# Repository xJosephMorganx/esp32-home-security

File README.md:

# ESP32 Home Security

**Four custom-built modules. One touchscreen hub. Local control over ESP-NOW.**

A modular residential monitoring project combining embedded software, custom KiCad PCBs, enclosure design, and local manufacturing. Four independent ESP32 firmwares connect a touchscreen hub, magnetic door sensor, PIR motion sensor, and RFID reader.

The hub owns the system state and card authorization. Sensor nodes report observations; the RFID reader requests actions. Internet services add WhatsApp, Messenger, and email notifications without being required for local supervision.

**Project status:** the latest project report documents completed hardware and successful functional integration of the four modules. It reports touch/RFID arming, card management, and notification delivery. These are project-reported hardware results, not automated test results or quantified reliability measurements.

## Highlights

- **Touchscreen control:** English UI on a 3.2-inch ILI9341 display with FT6336 capacitive touch, presented in 320 × 240 landscape.
- **Distributed sensing:** MC-38 door contact and PIR motion detection with filtering and explicit unknown/offline states.
- **RFID management:** hub-side authorization, enrollment, removal, and persistent storage for up to 32 card UIDs.
- **Encrypted local links:** provisioned ESP-NOW unicast peers, per-pair LMKs, application acknowledgements, deduplication, and automatic channel recovery.
- **Remote notifications:** WhatsApp and Messenger through CallMeBot; email through a Google Apps Script web app.
- **Local feedback:** confirmed-state LEDs, recent event history, and a red full-screen event alert with touch dismissal.
- **Clock and weather:** NTP time and Open-Meteo weather, with unavailable and stale-data indicators.

## Architecture

```mermaid
flowchart LR
    Door[Door sensor · MC-38] <-->|Encrypted ESP-NOW| Hub[ESP32 touchscreen hub]
    PIR[PIR motion sensor] <-->|Encrypted ESP-NOW| Hub
    RFID[RFID reader · RC522] <-->|Encrypted ESP-NOW| Hub
    Hub -->|Wi-Fi / HTTPS| Messages[CallMeBot · WhatsApp / Messenger]
    Hub -->|Wi-Fi / HTTPS| Email[Google Apps Script · Email]
    Hub -->|Wi-Fi| Services[NTP clock / Open-Meteo weather]
```

| Module | Responsibility | User feedback |
| --- | --- | --- |
| [Hub](firmware/hub/) | Global state, sensor supervision, card authorization, UI, and network services | Touchscreen and remote notifications |
| [Door](firmware/door/) | Debounce and report the magnetic contact | LED on only when armed and connected |
| [PIR](firmware/pir/) | Sensor warm-up, filtering, and motion reports | LED on only when armed and connected |
| [RFID](firmware/rfid/) | Read card presence and request actions from the hub | Green: disarmed; red: armed; both off without confirmed state |

Nodes do not need to join the router. When the hub is associated with Wi-Fi, ESP-NOW shares its channel. Nodes recover the channel through scanning and validated synchronization. Loss of internet does not itself disable local operation, although Wi-Fi association and channel changes can temporarily interrupt radio traffic.

The shared [application protocol](firmware/common/PROTOCOL.md) defines explicit binary serialization, session/sequence handling, retries, and `STATE_SYNC` acknowledgements. The [RFID contract](firmware/common/RFID_CONTRACT.md) adds short-lived operation contexts and correlated results. An ESP-NOW send callback alone is not proof that the hub processed an action.

## How it behaves

The hub starts **disarmed** after every reboot. Arming requires at least one connected sensor: door or PIR. RFID connectivity does not satisfy that requirement. Disarming does not require an online sensor.

An open door, active motion, or PIR warm-up does not independently block arming. While armed, admitted events can produce notifications and a red visual alert. The controller stays armed: although the protocol defines `ALARM` and `EXIT_DELAY`, the current controller does not transition into those states.

The UI provides **Home**, **Events**, **Nodes**, and **Setup**. Settings include diagnostics, touch testing, access cards, and notification tests. Card enrollment follows **Setup → Access cards → Add card → Scan card** and opens a 30-second enrollment window. Enrollment does not arm the system.

| Parameter | Current configuration / behavior |
| --- | --- |
| Link heartbeat / timeout | 5 seconds / 15 seconds |
| Report retries | Up to 3 transmissions, 250 ms apart |
| Channel search | 1 second per channel; not a total recovery-time guarantee |
| Door debounce | 40 ms |
| PIR setup in the reported build | 30-second warm-up, 10 ms sampling, 50 ms stability filter |
| RFID operation context / card removal | 5-second validity / 500 ms confirmed absence |
| Card storage | Up to 32 UIDs in a versioned, CRC-checked NVS blob |
| Event history | 16 entries in RAM |
| Notification queues | 16 entries per channel, expiring after 10 minutes |
| Visual alert | 10 seconds after drawing completes, or tap to close |

PIR electrical behavior and timing must be configured locally; the public template deliberately leaves unconfirmed settings unset. Queue contents and event history do not survive a reboot. Provider acceptance does not prove message receipt or reading.

## Repository layout

```text
firmware/
├── common/     Shared protocol library, contracts, and tests
├── hub/        Display, touch, state controller, radio, RFID authority, networking
├── door/       Door contact firmware and logic tests
├── pir/        PIR firmware, diagnostics, and tests
└── rfid/       RC522 firmware, diagnostics, and tests
hardware/
├── kicad/      Schematics, PCB layouts, and associated exports
├── hub/        Module manufacturing files
├── door/       Module manufacturing files
├── pir/        Module manufacturing files
└── rfid/       Module manufacturing files
```

Manufacturing assets include LightBurn laser projects and DXF files for CNC preparation. The STEP file alongside the door KiCad project is a **PCB 3D export**, not an enclosure model. The report describes enclosure design and completed assemblies; only files actually present in this repository are distributed here.

## Development environment

The report and inspected local environment identify the following baseline:

| Component | Version / source |
| --- | --- |
| Target | Classic ESP32, Arduino C++ |
| Arduino-ESP32 | 3.3.10 |
| Arduino CLI | 1.5.0 in the inspected environment |
| DomoticaProtocol | 1.2.0, included in `firmware/common` |
| MFRC522 | 1.4.12 |
| Adafruit GFX | 1.12.6 in the inspected environment |
| Adafruit BusIO | 1.17.4 in the inspected environment |
| Hub firmware identifier | `hub-wa-0.6.0` |
| Display / touch | Local SPI display driver and bundled FT6336 driver |

Wi-Fi, ESP-NOW, FreeRTOS, NVS, HTTPS, certificate-bundle support, and cJSON come from the ESP32 environment. The hub uses Adafruit GFX for drawing primitives; it does not use the manufacturer's TFT_eSPI or LVGL demo as its display initialization.

### Configure your own devices

Clone the repository, install the ESP32 board support and listed Arduino libraries, then create local configuration files from the templates:

| Module | Copy this template | To this ignored local file |
| --- | --- | --- |
| Hub Wi-Fi | `firmware/hub/secrets.example.h` | `firmware/hub/secrets.h` |
| Hub radio | `firmware/hub/radio_secrets.example.h` | `firmware/hub/radio_secrets.h` |
| WhatsApp | `firmware/hub/whatsapp_secrets.example.h` | `firmware/hub/whatsapp_secrets.h` |
| Messenger | `firmware/hub/messenger_secrets.example.h` | `firmware/hub/messenger_secrets.h` |
| Email | `firmware/hub/email_secrets.example.h` | `firmware/hub/email_secrets.h` |
| Door | `firmware/door/config.example.h` | `firmware/door/config.local.h` |
| PIR | `firmware/pir/config.example.h` | `firmware/pir/config.local.h` |
| RFID | `firmware/rfid/config.example.h` | `firmware/rfid/config.local.h` |

Provision your own STA MAC addresses, explicit PMK, and unique LMK for each hub/node pair. Matching peers must use compatible keys. Some public node examples retain a project-specific hub MAC: replace it with your own; it is not a discovery default. Verify input polarity, LED polarity, sensor readiness settings, and permitted channels before enabling provisioned operation. Empty or invalid credentials do not enable an unencrypted fallback.

Configure only the notification channels you intend to use. Email requires a separately deployed Google Apps Script endpoint with `HUB_SECRET` and `EMAIL_TO` properties; that deployment is not included in this repository. Keep the matching shared secret in the ignored hub configuration. Never put real Wi-Fi credentials, notification API keys, phone numbers, or radio keys in example files.

### Build and upload

Each module is a separate sketch. From the repository root, supply the shared library explicitly, for example:

```sh
arduino-cli compile --fqbn esp32:esp32:esp32 --library ./firmware/common ./firmware/hub
arduino-cli compile --fqbn esp32:esp32:esp32 --library ./firmware/common ./firmware/door
arduino-cli compile --fqbn esp32:esp32:esp32 --library ./firmware/common ./firmware/pir
arduino-cli compile --fqbn esp32:esp32:esp32 --library ./firmware/common ./firmware/rfid
```

Use the board definition and flash settings appropriate to your ESP32 board. Upload each sketch to its corresponding module using Arduino IDE or Arduino CLI and the actual serial port. The external enclosure USB-C connector supplies power only; the report describes opening the enclosure to reach the ESP32 programming port.

These commands are build instructions, not a claim that a fresh build or hardware test was run for this README. Source-level tests are included under each module's `tests/` directory and under `firmware/common/tests/`.

## Hardware and fabrication

The reported assemblies use four custom single-sided PCBs, separate enclosures, and individual 5 V supplies through two-wire USB-C power connectors. The RC522 operates from 3.3 V. PCB preparation combines KiCad design, laser removal of a paint mask, chemical etching, UV solder mask, and CNC drilling/outline cutting.

The hub's fixed PCB wiring is:

| Interface | GPIO assignments |
| --- | --- |
| LCD | CS 18, RST 19, DC 21, MOSI 22, SCK 23, MISO 33, backlight 32 |
| Touch | SCL 25, RST 26, SDA 27, INT 14 |
| Unused SD select | CS 13, held high |

The LCD runs at 1 MHz SPI; touch uses 100 kHz I2C. Do not replace these assignments with manufacturer demo wiring.

For RFID, the latest report and [current board definitions](firmware/rfid/board_pins.h) agree on SS 17, RST 23, SCK 18, MISO 21, MOSI 19, and IRQ 22, with green/red LEDs on 25/26. These differ from an older project context table (SS 21, RST 22, MISO 19, MOSI 23); the source records an explicit user correction. Confirm the actual board wiring before reproducing the assembly.

## Validation and limitations

The latest project report, *Sistema modular de domótica y seguridad residencial con ESP32*, documents completed assemblies and functional checks of inter-module communication, touch/RFID arming and disarming, card management, WhatsApp/Messenger/email notifications, and visual-alert dismissal. The report is maintained outside the public repository.

The project is an academic monitoring prototype, with these documented limits:

- Touch controls and card administration have no PIN or administrator authentication.
- RFID authorization uses a card UID, which can be copied; it is not cryptographic card authentication.
- The system starts disarmed after reboot and has no battery backup, siren, or physical lock actuator.
- Event history and notification queues are bounded and volatile; remote delivery depends on external services.
- Radio recovery can involve interruptions. No measured range, latency, packet-loss, or power-consumption figures are claimed.
- Touch-panel electrical levels have not been fully characterized across operating conditions.
- No residential alarm, electrical, or environmental certification is claimed.

## What is kept local

The public repository includes firmware, configuration examples, protocol documentation, tests, and hardware/manufacturing sources. `.gitignore` excludes real secrets, local node configuration, build outputs, caches, KiCad internal histories/preferences, `AGENTS.md`, and the root `docs/`, `escuela/`, and `references/` folders.

The original manufacturer package and academic report are not bundled. Removing a file from tracking does not remove it from earlier commits; older context and reference files remain in repository history.

## Third-party notices

Preserve notices in bundled source files and the [font license](firmware/hub/FONT_LICENSE.txt). External dependencies retain their own licenses. No repository-wide license has been declared.

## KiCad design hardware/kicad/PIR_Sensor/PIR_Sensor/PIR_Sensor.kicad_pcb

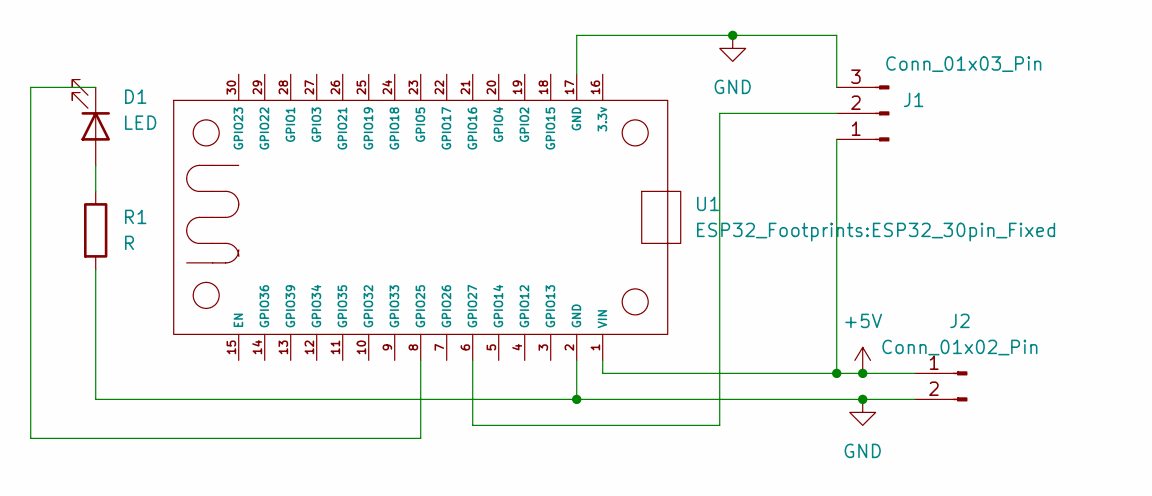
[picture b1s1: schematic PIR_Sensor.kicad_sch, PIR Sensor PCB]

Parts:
D1: LED; LED_D5.0mm
J1: Conn_01x03_Pin; PinHeader_1x03_P2.54mm_Vertical
J2: Conn_01x02_Pin; PinHeader_1x02_P2.54mm_Vertical
R1: R; R_Axial_DIN0207_L6.3mm_D2.5mm_P7.62mm_Horizontal
U1: ESP32_30pin_Fixed

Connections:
+5V: J1.1, J2.1, U1.1 (VIN)
GND: J1.3, J2.2, R1.2, U1.2 (GND), U1.17 (GND)
unnamed: D1.2 (A), R1.1
unnamed: D1.1 (K), U1.8 (GPIO25)
unnamed: J1.2, U1.6 (GPIO27)

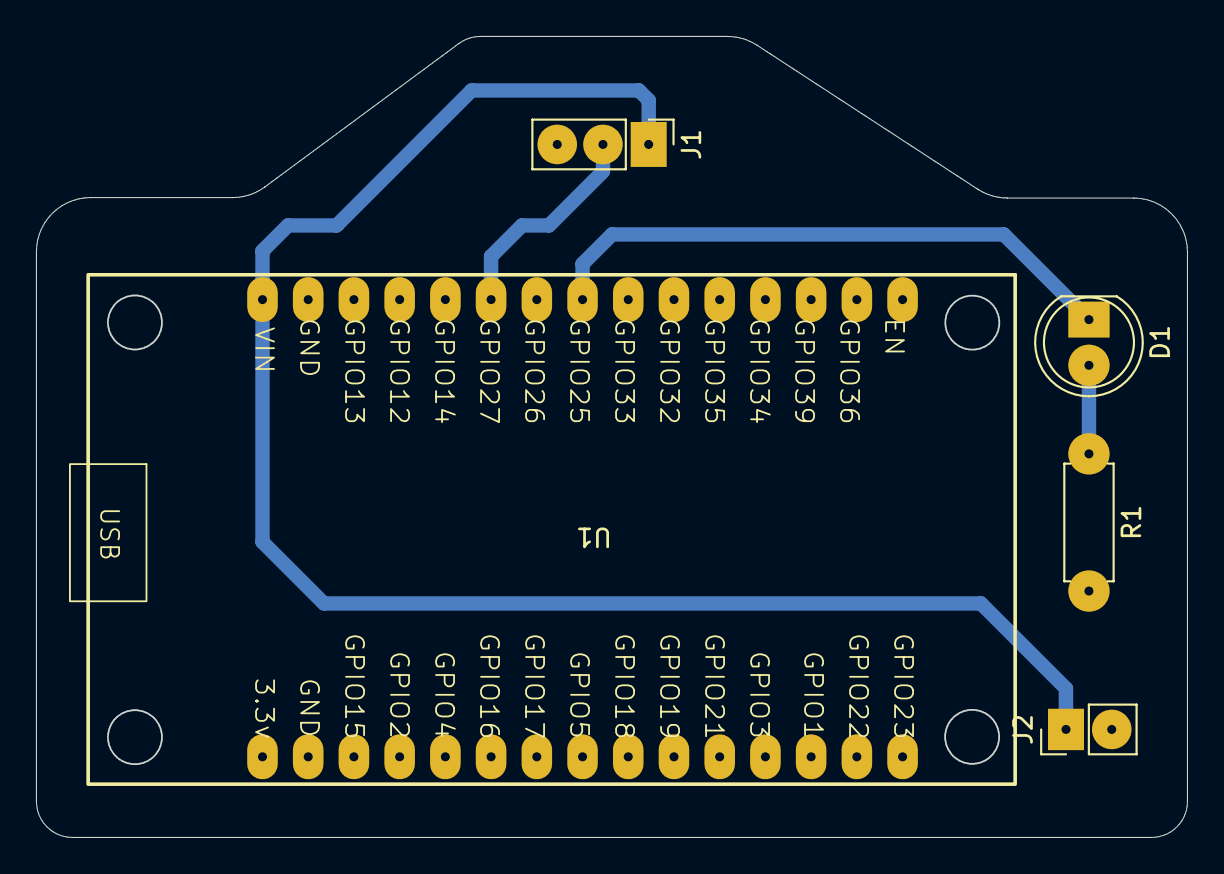
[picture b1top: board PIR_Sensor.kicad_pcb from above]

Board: 2 copper layers, 63.9 x 44.5 mm, 5 parts (0 on the bottom side), 5 nets.

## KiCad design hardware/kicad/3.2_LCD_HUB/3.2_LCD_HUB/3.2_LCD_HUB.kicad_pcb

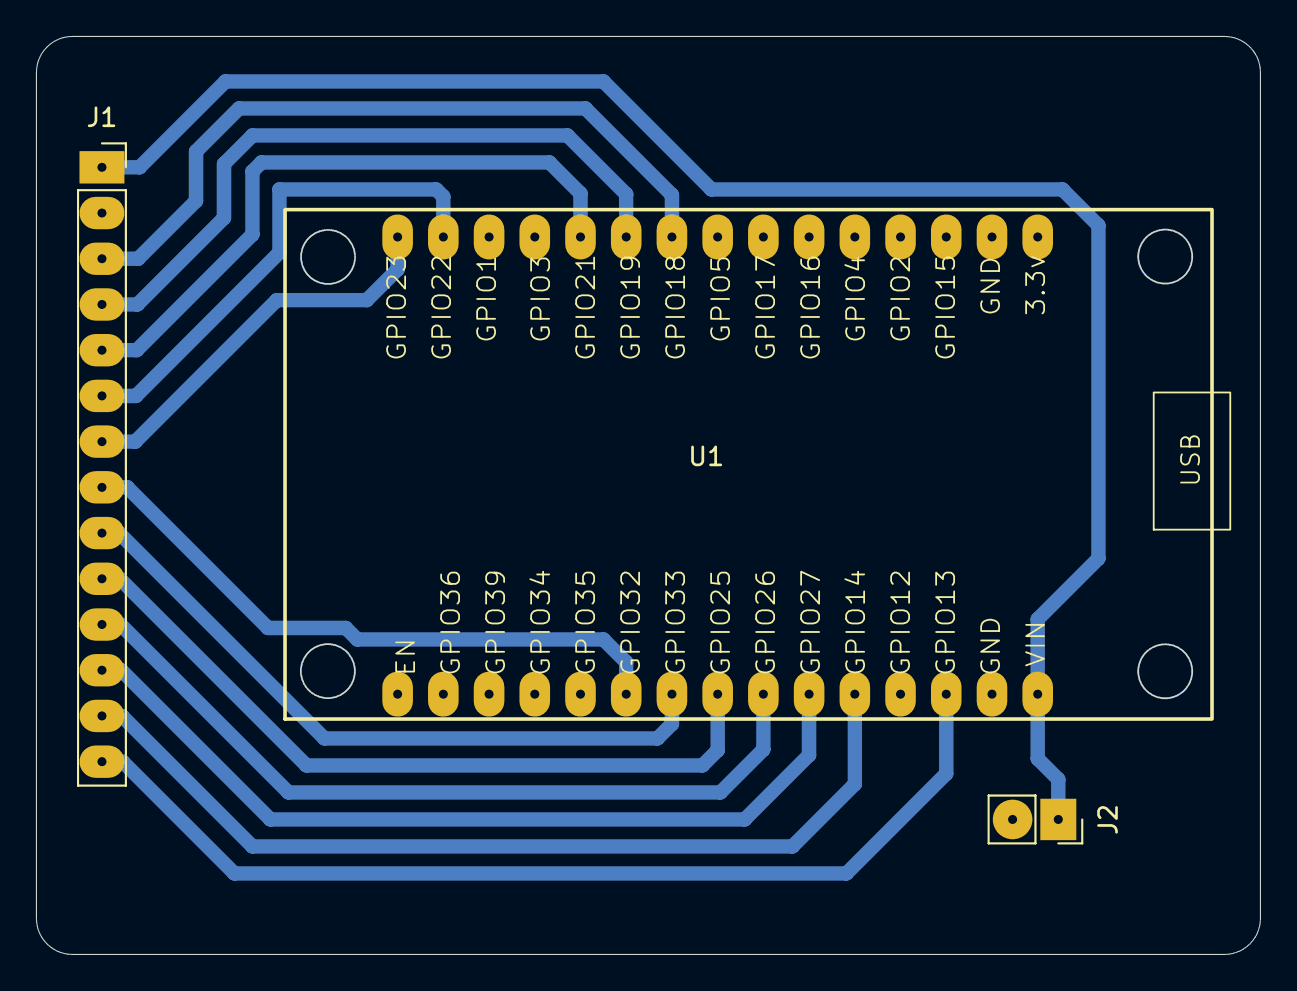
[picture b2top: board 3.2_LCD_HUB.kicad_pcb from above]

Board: 2 copper layers, 68.0 x 51.0 mm, 3 parts (0 on the bottom side), 14 nets.

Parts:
J1: Conn_01x14_Socket; PinSocket_1x14_P2.54mm_Vertical
J2: Conn_01x02_Socket; PinSocket_1x02_P2.54mm_Vertical
U1: ESP32_30pin_Fixed

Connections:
GND: J1.2, J2.2, U1.2 (GND), U1.17 (GND)
unnamed: J1.1, J2.1, U1.1 (VIN)
unnamed: J1.3, U1.24 (GPIO18)
unnamed: J1.4, U1.25 (GPIO19)
unnamed: J1.5, U1.26 (GPIO21)
unnamed: J1.6, U1.29 (GPIO22)
unnamed: J1.7, U1.30 (GPIO23)
unnamed: J1.8, U1.10 (GPIO32)
unnamed: J1.9, U1.9 (GPIO33)
unnamed: J1.10, U1.8 (GPIO25)
unnamed: J1.11, U1.7 (GPIO26)
unnamed: J1.12, U1.6 (GPIO27)
unnamed: J1.13, U1.5 (GPIO14)
unnamed: J1.14, U1.3 (GPIO13)

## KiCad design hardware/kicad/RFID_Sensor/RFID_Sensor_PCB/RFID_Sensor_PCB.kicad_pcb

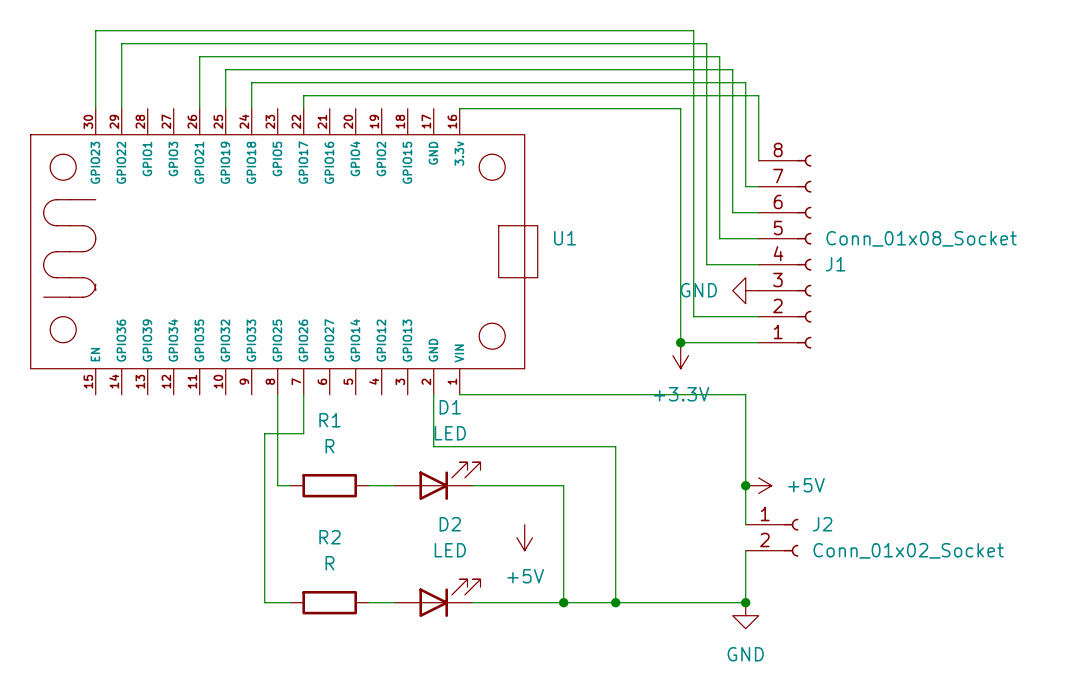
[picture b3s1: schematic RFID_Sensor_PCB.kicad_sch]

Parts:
D1, D2: LED; LED_D5.0mm
J1: Conn_01x08_Socket; RFID-RC522
J2: Conn_01x02_Socket; PinSocket_1x02_P2.54mm_Vertical
R1, R2: R; R_Axial_DIN0207_L6.3mm_D2.5mm_P7.62mm_Horizontal
U1: ESP32_30pin_Fixed

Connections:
+3.3V: J1.1, U1.16 (3.3v)
+5V: J2.1, U1.1 (VIN)
GND: D1.1 (K), D2.1 (K), J1.3, J2.2, U1.2 (GND)
unnamed: D1.2 (A), R1.1
unnamed: D2.2 (A), R2.1
unnamed: J1.2, U1.30 (GPIO23)
unnamed: J1.4, U1.29 (GPIO22)
unnamed: J1.5, U1.26 (GPIO21)
unnamed: J1.6, U1.25 (GPIO19)
unnamed: J1.7, U1.24 (GPIO18)
unnamed: J1.8, U1.22 (GPIO17)
unnamed: R1.2, U1.8 (GPIO25)
unnamed: R2.2, U1.7 (GPIO26)

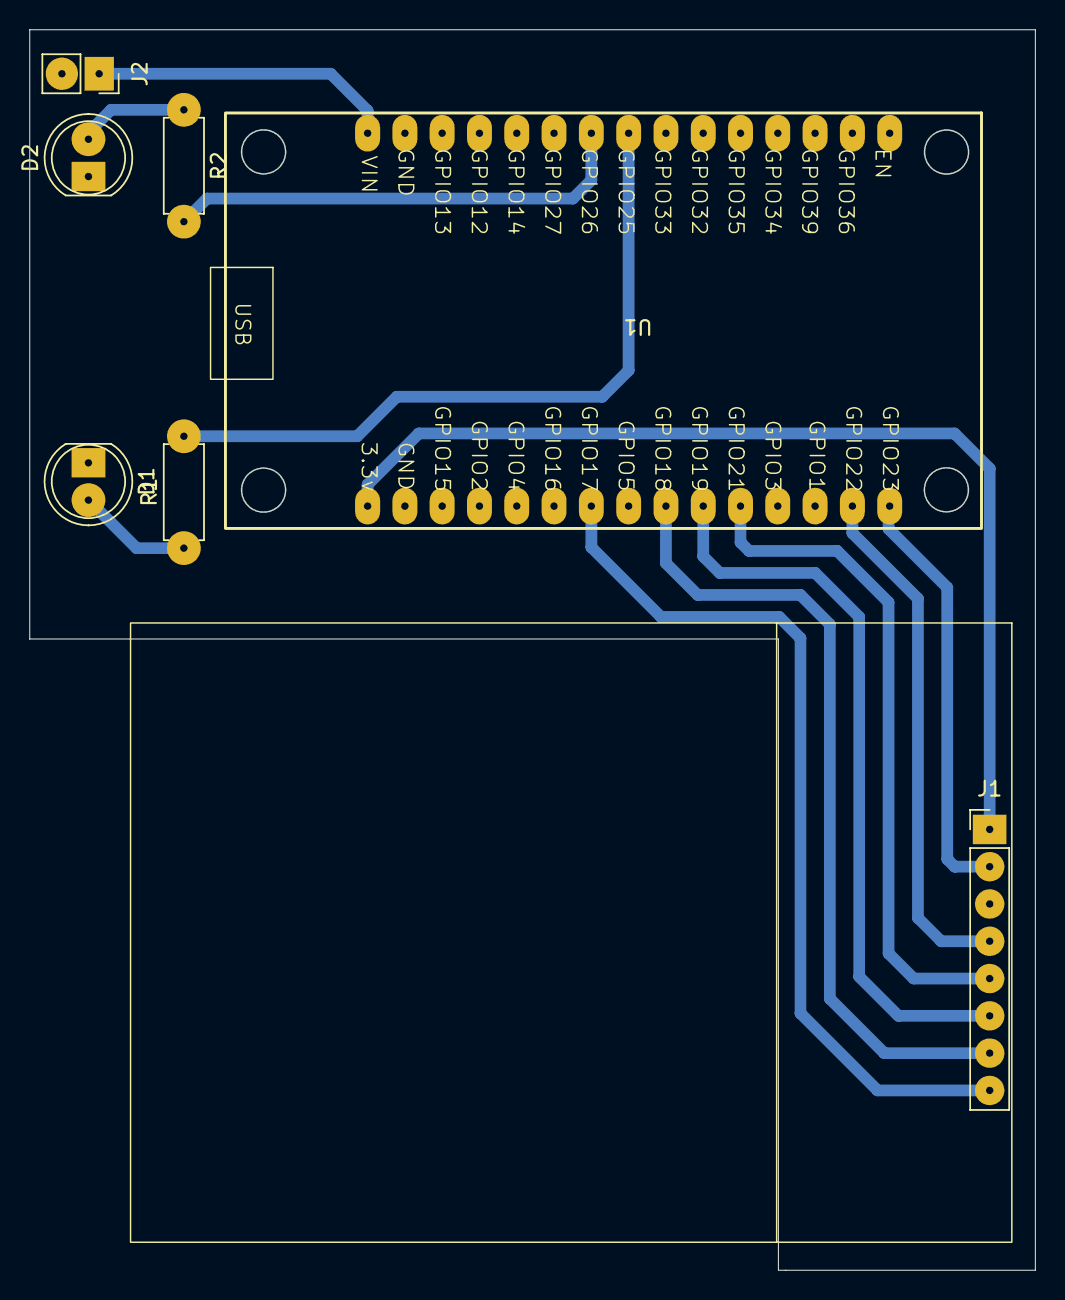
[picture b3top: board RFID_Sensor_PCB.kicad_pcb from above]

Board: 2 copper layers, 68.5 x 84.5 mm, 7 parts (0 on the bottom side), 13 nets.

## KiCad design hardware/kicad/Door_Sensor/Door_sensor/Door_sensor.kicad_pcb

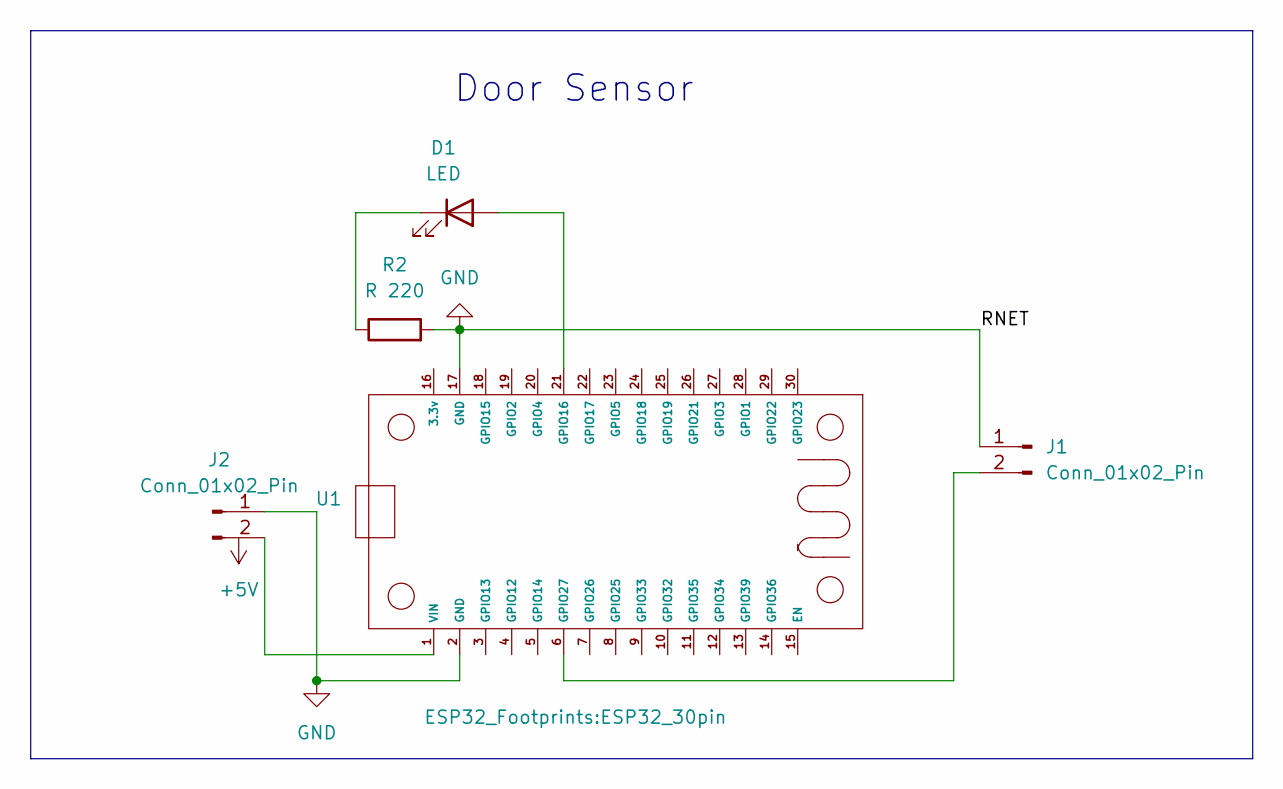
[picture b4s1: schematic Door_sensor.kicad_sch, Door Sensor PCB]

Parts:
D1: LED; LED_D5.0mm
J1: Conn_01x02_Pin; PinHeader_1x02_P2.54mm_Horizontal
J2: Conn_01x02_Pin; SolderWire-0.15sqmm_1x02_P4mm_D0.5mm_OD1.5mm
R2: R 220; R_Axial_DIN0207_L6.3mm_D2.5mm_P10.16mm_Horizontal
U1: ESP32_30pin

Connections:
/<NO NET>: J1.2, U1.6 (GPIO27)
GND: J1.1, J2.1, R2.2, U1.2 (GND), U1.17 (GND)
unnamed: D1.2 (A), U1.21 (GPIO16)
unnamed: D1.1 (K), R2.1
unnamed: J2.2, U1.1 (VIN)

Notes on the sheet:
Door Sensor

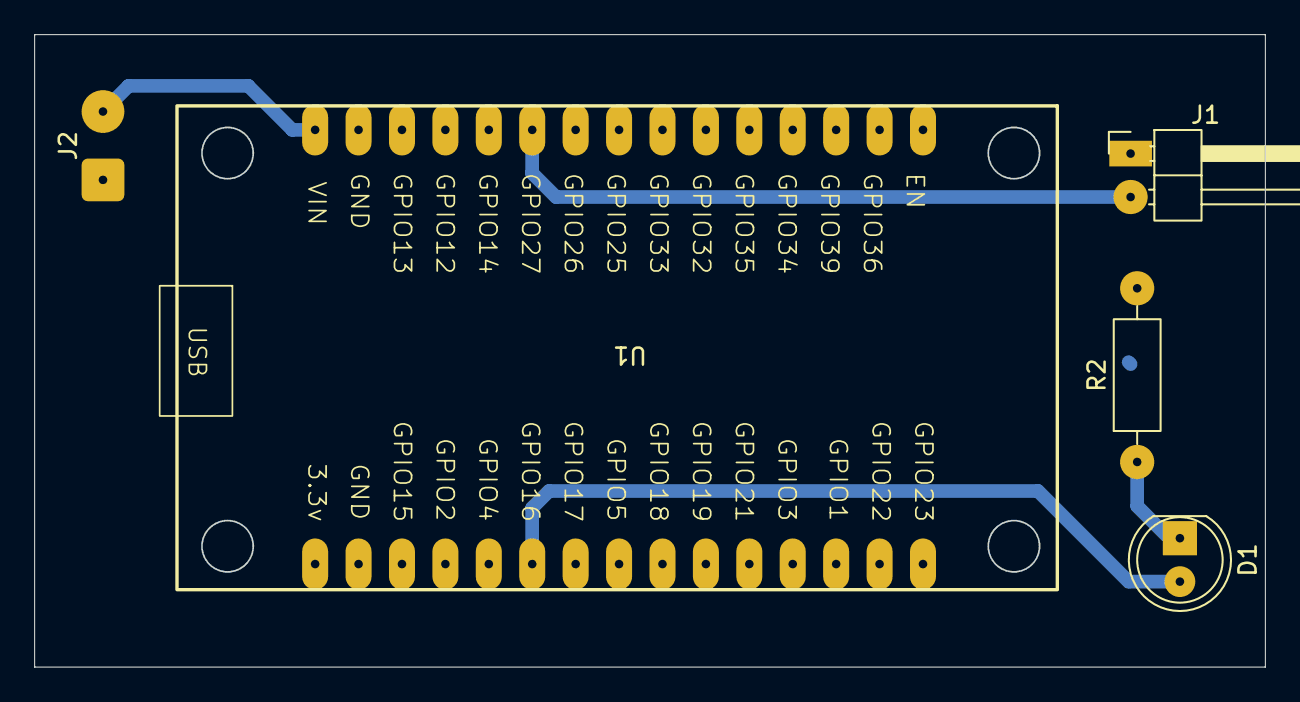
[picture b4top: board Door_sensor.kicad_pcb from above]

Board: 2 copper layers, 72.0 x 37.0 mm, 5 parts (0 on the bottom side), 5 nets.
